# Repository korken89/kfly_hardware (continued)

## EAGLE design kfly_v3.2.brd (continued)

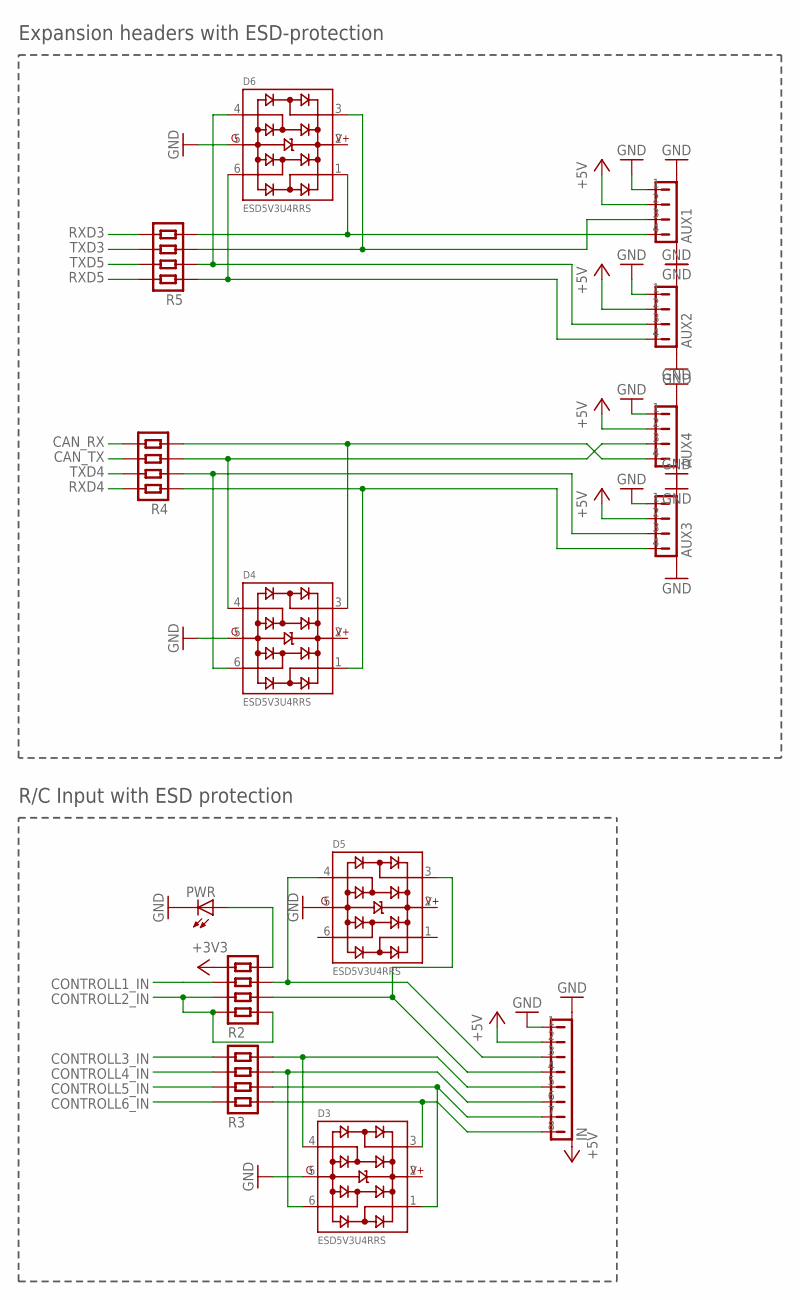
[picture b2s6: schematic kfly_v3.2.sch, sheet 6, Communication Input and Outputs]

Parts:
AUX1, AUX2, AUX3, AUX4: JST-4PIN-SIDE-1.0; JST-4PIN-SIDE
D3, D4, D5, D6: ESD5V3U4RRS; SOT363
IN: JST-8PIN-SIDE-1.0; JST-8PIN-SIDE
PWR: LED0603; LED-0603
R2, R3, R4, R5: RESISTOR-4ARRAY-0804; RESISTORARRAY_0804

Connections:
+3V3: R2.4; also elsewhere on the board
+5V: AUX1.2, AUX2.2, AUX3.2, AUX4.2, IN.2, IN.NC2 (GND2); also elsewhere on the board
CAN_RX: R4.5; also elsewhere on the board
CAN_TX: R4.6; also elsewhere on the board
CONTROLL1_IN: R2.3; also elsewhere on the board
CONTROLL2_IN: R2.1, R2.2, R2.8; also elsewhere on the board
CONTROLL3_IN: R3.4; also elsewhere on the board
CONTROLL4_IN: R3.3; also elsewhere on the board
CONTROLL5_IN: R3.2; also elsewhere on the board
CONTROLL6_IN: R3.1; also elsewhere on the board
GND: AUX1.1, AUX1.NC1 (P1), AUX1.NC2 (P2), AUX2.1, AUX2.NC1 (P1), AUX2.NC2 (P2), AUX3.1, AUX3.NC1 (P1), AUX3.NC2 (P2), AUX4.1, AUX4.NC1 (P1), AUX4.NC2 (P2), D3.5, D4.5, D5.5, D6.5, IN.1, IN.NC1 (GND1), PWR.C; also elsewhere on the board
unnamed: AUX2.3, D6.4, R5.2
unnamed: PWR.A, R2.5
unnamed: AUX3.3, D4.6, R4.2
unnamed: D5.4, IN.3, R2.6
unnamed: D3.3, IN.8, R3.8
unnamed: D3.4, IN.5, R3.5
unnamed: AUX4.4, D4.3, R4.4
unnamed: AUX4.3, D4.4, R4.3
unnamed: AUX3.4, D4.1, R4.1
unnamed: D3.1, IN.7, R3.7
unnamed: D3.6, IN.6, R3.6
unnamed: AUX1.3, D6.3, R5.3
unnamed: AUX2.4, D6.6, R5.1
unnamed: D5.3, IN.4, R2.7
unnamed: AUX1.4, D6.1, R5.4
RXD3: R5.5; also elsewhere on the board
RXD4: R4.8; also elsewhere on the board
RXD5: R5.8; also elsewhere on the board
TXD3: R5.6; also elsewhere on the board
TXD4: R4.7; also elsewhere on the board
TXD5: R5.7; also elsewhere on the board

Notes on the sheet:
Expansion headers with ESD-protection
R/C Input with ESD protection

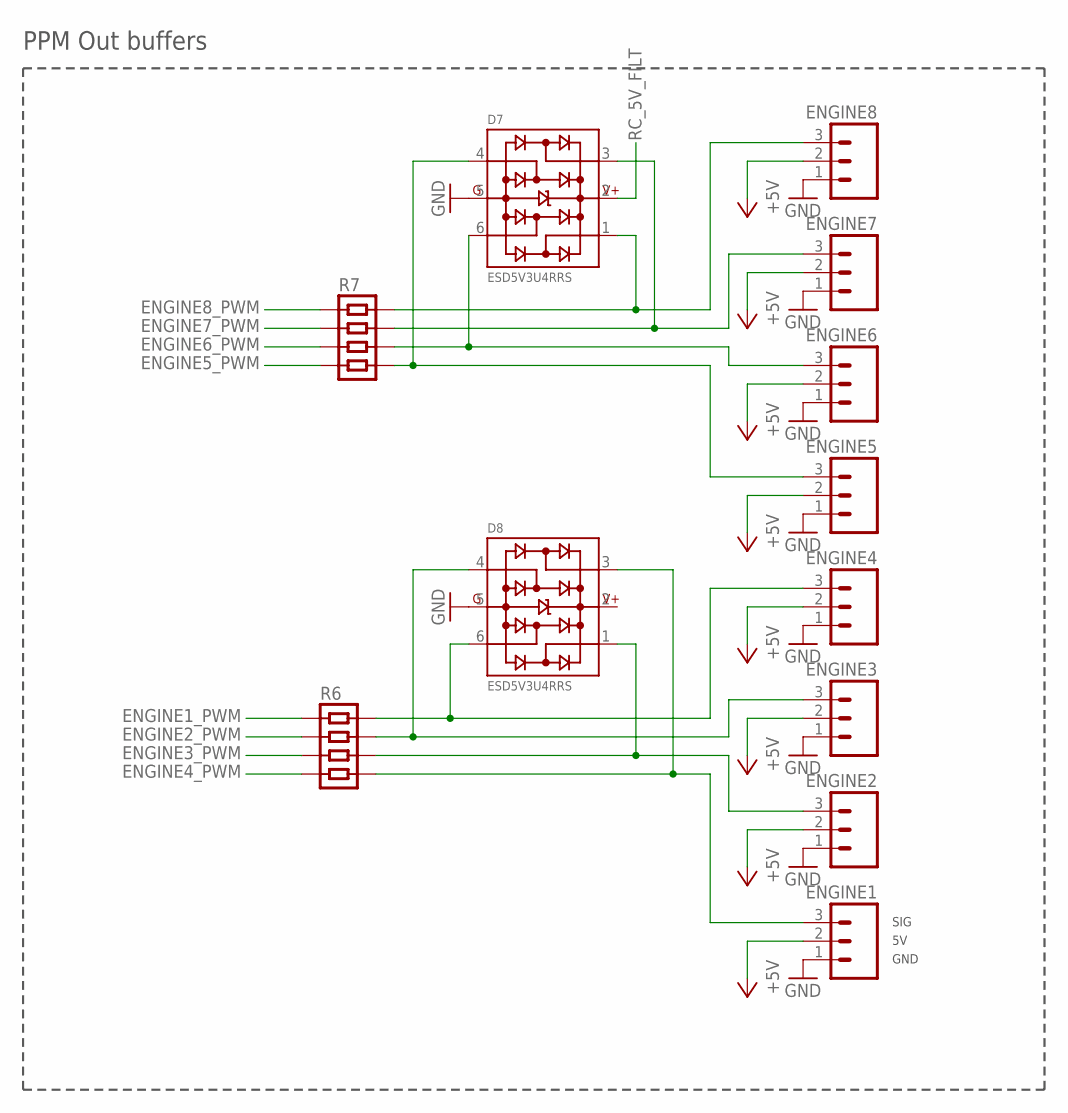
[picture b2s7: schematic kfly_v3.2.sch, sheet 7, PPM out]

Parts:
D7, D8: ESD5V3U4RRS; SOT363
ENGINE1, ENGINE2, ENGINE3, ENGINE4, ENGINE5, ENGINE6, ENGINE7, ENGINE8: M03TH_90DEG; M03_90DEG
R6, R7: RESISTOR-4ARRAY-0804; RESISTORARRAY_0804

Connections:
+5V: ENGINE1.2, ENGINE2.2, ENGINE3.2, ENGINE4.2, ENGINE5.2, ENGINE6.2, ENGINE7.2, ENGINE8.2; also elsewhere on the board
ENGINE1_PWM: R6.1; also elsewhere on the board
ENGINE2_PWM: R6.2; also elsewhere on the board
ENGINE3_PWM: R6.3; also elsewhere on the board
ENGINE4_PWM: R6.4; also elsewhere on the board
ENGINE5_PWM: R7.4; also elsewhere on the board
ENGINE6_PWM: R7.3; also elsewhere on the board
ENGINE7_PWM: R7.2; also elsewhere on the board
ENGINE8_PWM: R7.1; also elsewhere on the board
GND: D7.5, D8.5, ENGINE1.1, ENGINE2.1, ENGINE3.1, ENGINE4.1, ENGINE5.1, ENGINE6.1, ENGINE7.1, ENGINE8.1; also elsewhere on the board
unnamed: D7.1, ENGINE8.3, R7.8
unnamed: D7.3, ENGINE7.3, R7.7
unnamed: D7.6, ENGINE6.3, R7.6
unnamed: D7.4, ENGINE5.3, R7.5
unnamed: D8.1, ENGINE2.3, R6.6
unnamed: D8.3, ENGINE1.3, R6.5
unnamed: D8.6, ENGINE4.3, R6.8
unnamed: D8.4, ENGINE3.3, R6.7
RC_5V_FILT: D7.2; also elsewhere on the board

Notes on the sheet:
PPM Out buffers
GND
SIG

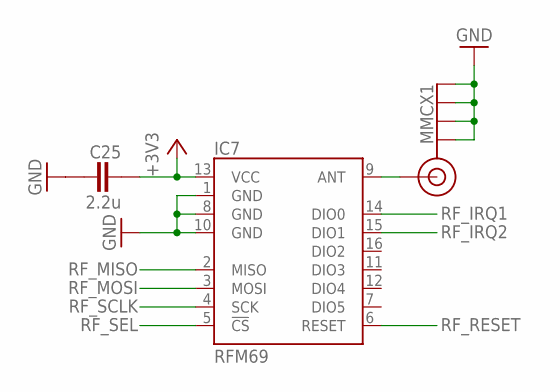
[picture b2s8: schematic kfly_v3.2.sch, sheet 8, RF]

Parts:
C25: 2.2u; CAPC1005X60N
IC7: RFM69
MMCX1: MMCX; MMCX_THROUGHHOLE_RIGHTANGLE

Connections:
+3V3: C25.1, IC7.13 (VCC); also elsewhere on the board
GND: C25.2, IC7.1 (GND), IC7.8 (GND), IC7.10 (GND), MMCX1.G1 (GND), MMCX1.G2 (GND), MMCX1.G3 (GND), MMCX1.G4 (GND); also elsewhere on the board
unnamed: IC7.9 (ANT), MMCX1.S (SIGNAL)
RF_IRQ1: IC7.14 (DIO0); also elsewhere on the board
RF_IRQ2: IC7.15 (DIO1); also elsewhere on the board
RF_MISO: IC7.2 (MISO); also elsewhere on the board
RF_MOSI: IC7.3 (MOSI); also elsewhere on the board
RF_RESET: IC7.6 (RESET); also elsewhere on the board
RF_SCLK: IC7.4 (SCK); also elsewhere on the board
RF_SEL: IC7.5 (!CS); also elsewhere on the board

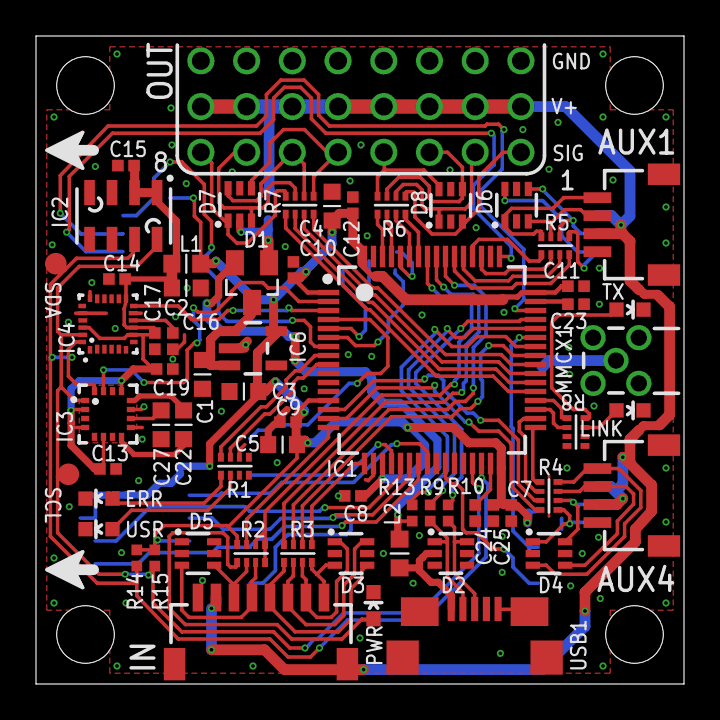
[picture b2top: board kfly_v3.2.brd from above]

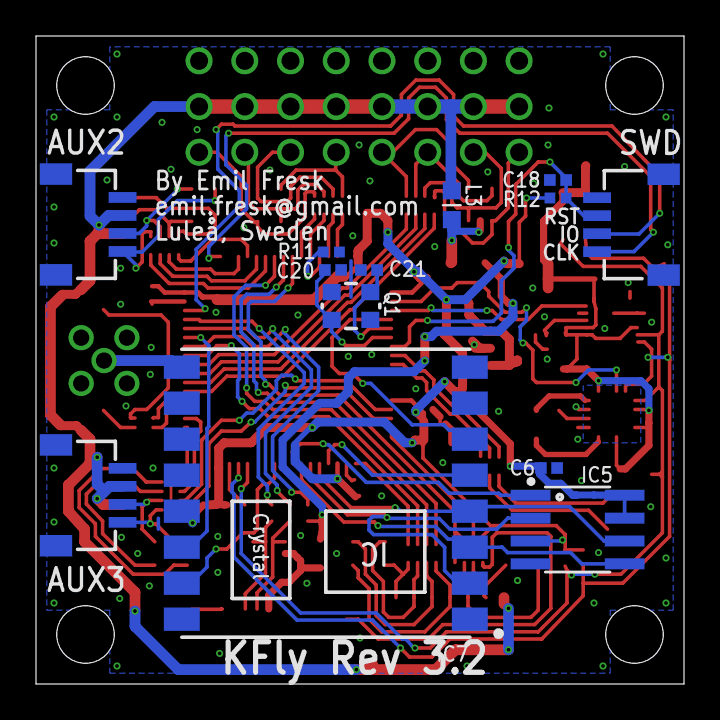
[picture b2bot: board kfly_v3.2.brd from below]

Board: 4 copper layers, 36.0 x 36.0 mm, 83 parts (13 on the bottom side), 91 nets.
